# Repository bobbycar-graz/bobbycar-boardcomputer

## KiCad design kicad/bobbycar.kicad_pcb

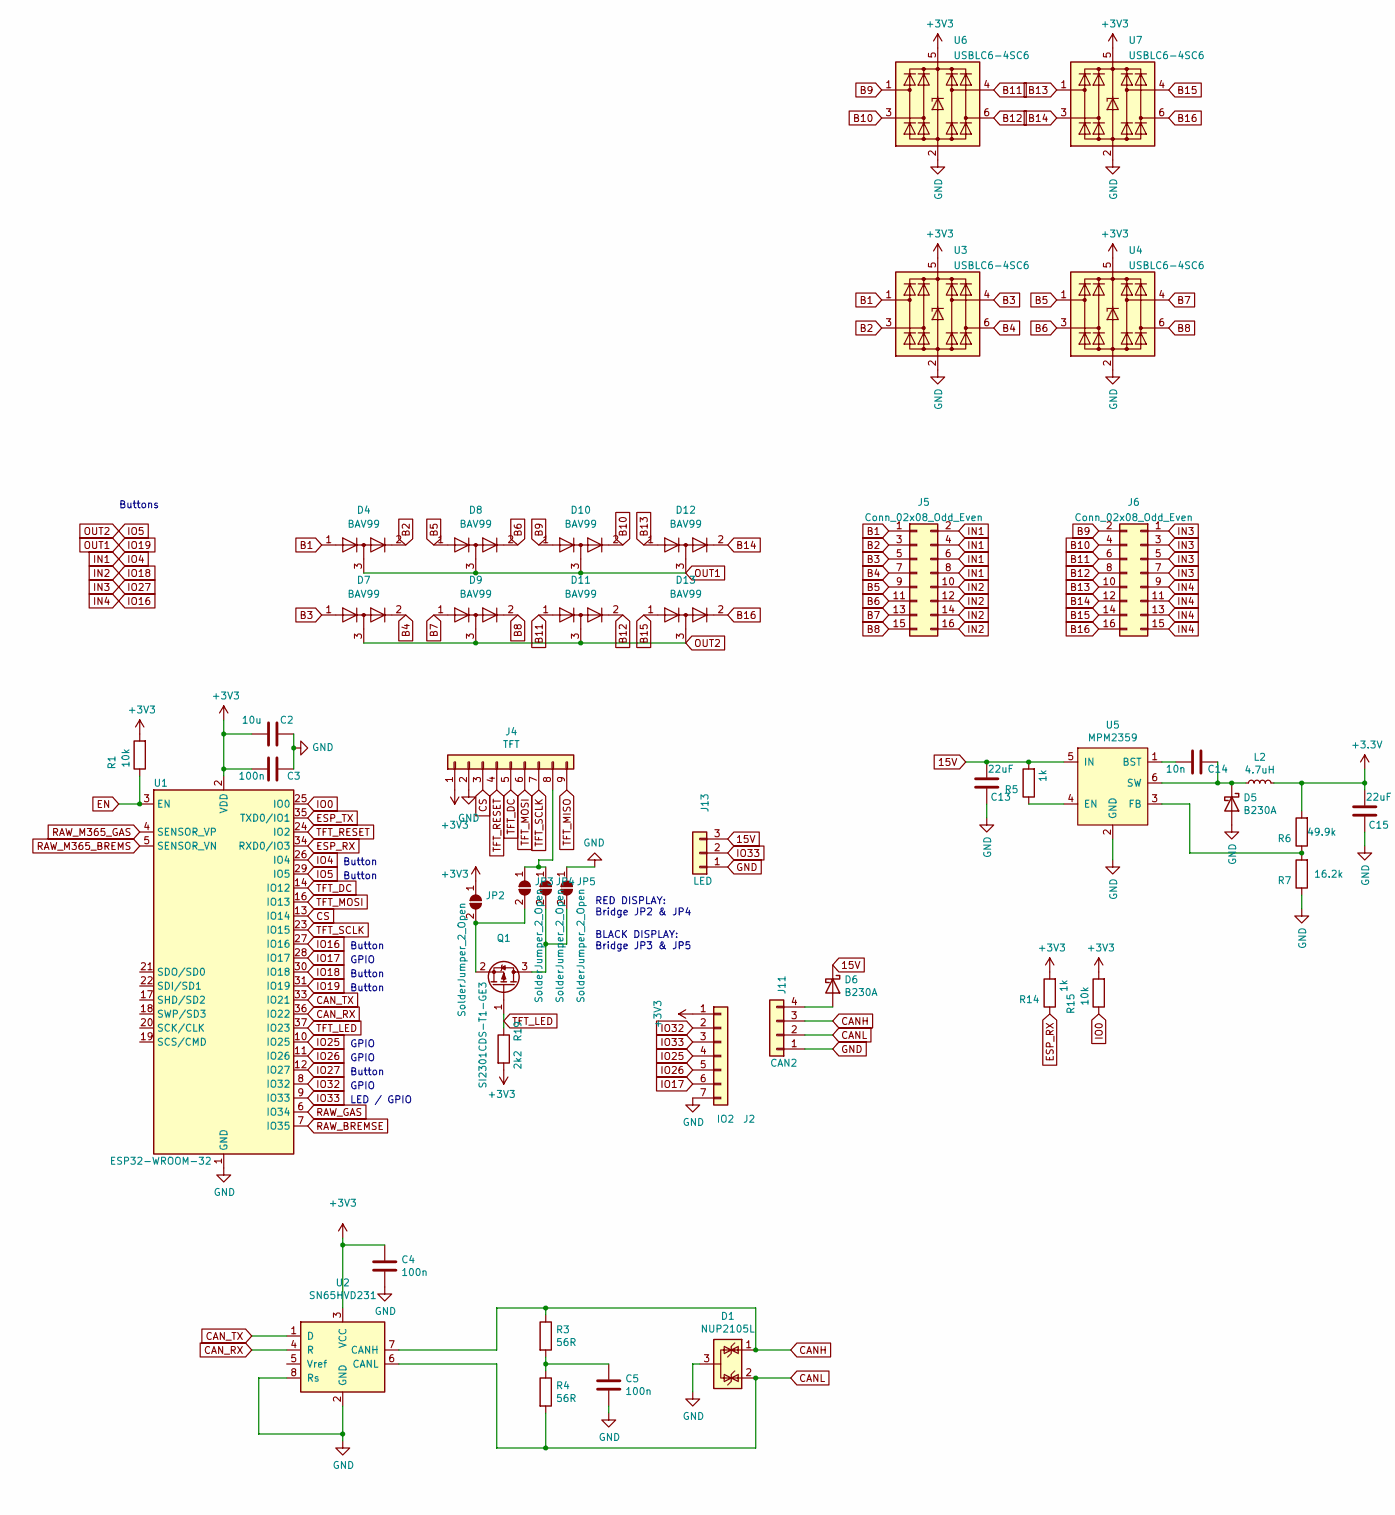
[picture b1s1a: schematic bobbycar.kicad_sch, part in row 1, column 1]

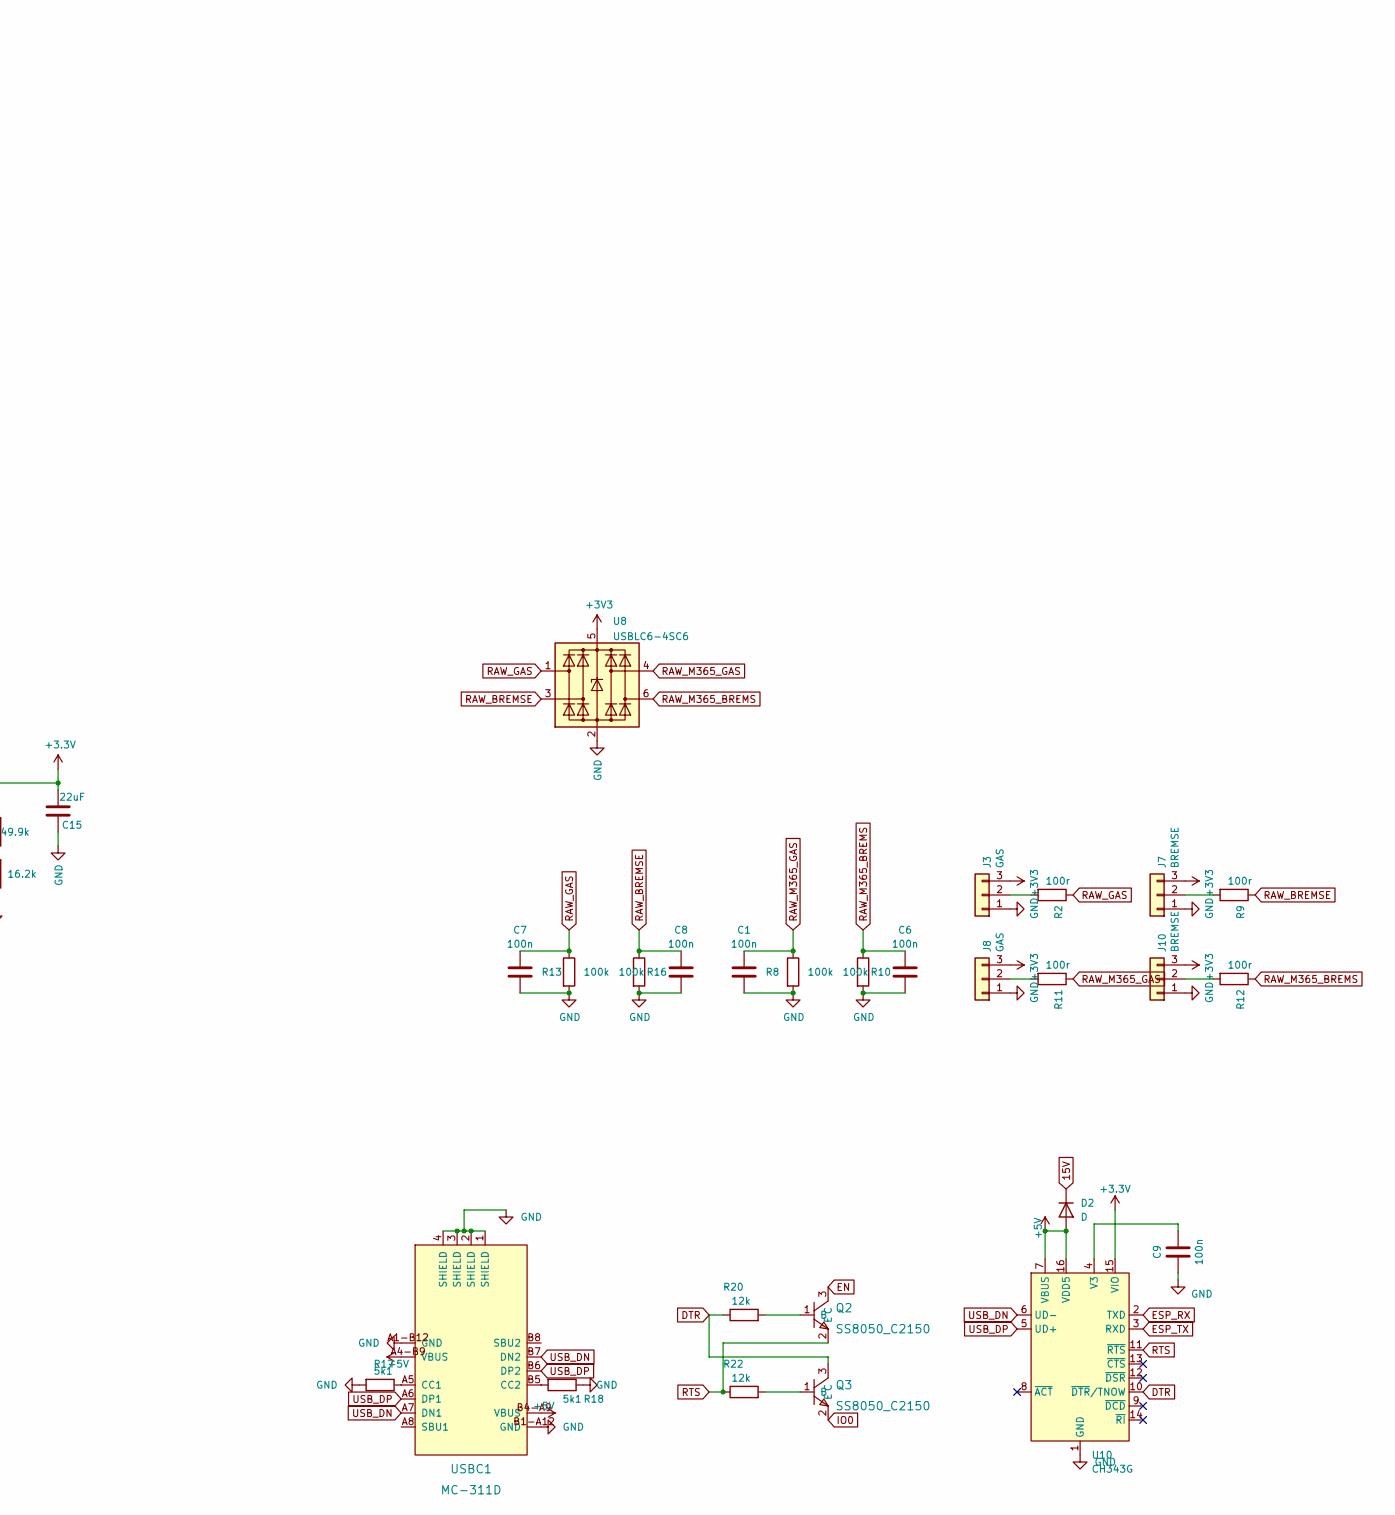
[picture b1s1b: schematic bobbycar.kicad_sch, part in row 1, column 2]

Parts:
C1, C3, C4, C5, C6, C7, C8, C9: 100n; C_0603_1608Metric; LCSC Part # C14663
C2: 10u; C_0603_1608Metric; LCSC Part # C19702
C13, C15: 22uF; C_0805_2012Metric; LCSC Part # C45783
C14: 10n; C_0603_1608Metric; LCSC Part # C57112
D1: NUP2105L; SOT-23; LCSC Part # C284104
D2: D; D_SOD-123; LCSC Part # C8598
D4: BAV99; SOT-23; LCSC Part # C2500
D5, D6: B230A; D_SMA; LCSC Part # C12889
D7, D8, D9, D10, D11, D12, D13: BAV99; SOT-23
J2: IO2; PinHeader_2x04_P2.54mm_Vertical_7Pin
J3, J8: GAS; PinHeader_1x03_P2.54mm_Vertical; LCSC Part # DNP
J4: TFT; PinSocket_1x09_P2.54mm_Vertical; LCSC Part # DNP
J5, J6: Conn_02x08_Odd_Even; PinHeader_2x08_P2.54mm_Vertical; LCSC Part # DNP
J7, J10: BREMSE; PinHeader_1x03_P2.54mm_Vertical; LCSC Part # DNP
J11: CAN2; JST_XH_B4B-XH-A_1x04_P2.50mm_Vertical; LCSC Part # C144395
J13: LED; JST_XH_B3B-XH-A_1x03_P2.50mm_Vertical
JP2, JP3, JP4, JP5: SolderJumper_2_Open; SolderJumper-2_P1.3mm_Open_RoundedPad1.0x1.5mm
L2: 4.7uH; L_5040; LCSC Part # C354606
Q1: SI2301CDS-T1-GE3; SOT-23; LCSC Part # C10487
Q2, Q3: SS8050_C2150; TSOT-23; LCSC Part C2150
R1, R15: 10k; R_0603_1608Metric; LCSC C25804
R2, R9, R11, R12: 100r; R_0603_1608Metric; LCSC Part # C22775
R3, R4: 56R; R_0603_1608Metric; LCSC Part # C25196
R5, R14: 1k; R_0603_1608Metric; LCSC Part # C21190
R6: 49.9k; R_0603_1608Metric; LCSC Part # C23184
R7: 16.2k; R_0603_1608Metric; LCSC Part # C22885
R8, R10, R13, R16: 100k; R_0603_1608Metric; LCSC Part # C21190
R17, R18: 5k1; R_0603_1608Metric; LCSC C23186
R19: 2k2; R_0603_1608Metric; LCSC Part # C4190
R20, R22: 12k; R_0603_1608Metric; LCSC C22790
U1: ESP32-WROOM-32; LCSC Part # C701343
U2: SN65HVD231; SOIC-8_3.9x4.9mm_P1.27mm; LCSC Part # C30530
U3, U4, U6, U7: USBLC6-4SC6; SOT-23-6; LCSC Part # C558419
U5: MPM2359; SOT-23-6; LCSC Part # C2959845
U8: USBLC6-4SC6; SOT-23-6
U10: CH343G; SOIC-16_3.9x9.9mm_P1.27mm; LCSC C2844153
USBC1: MC-311D; USB-C-SMD_MC-311D; LCSC Part C136423

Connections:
15V: C13.2, D2.1 (K), D6.1 (K), J13.3, R5.2, U5.5 (IN)
+5V: D2.2 (A), U10.7 (VBUS), U10.16 (VDD5), USBC1.A4-B9 (VBUS), USBC1.B4-A9 (VBUS)
B1: D4.1 (K), J5.1, U3.1 (I/O1)
B2: D4.2 (A), J5.3, U3.3 (I/O2)
B3: D7.1 (K), J5.5, U3.4 (I/O3)
B4: D7.2 (A), J5.7, U3.6 (I/O4)
B5: D8.1 (K), J5.9, U4.1 (I/O1)
B6: D8.2 (A), J5.11, U4.3 (I/O2)
B7: D9.1 (K), J5.13, U4.4 (I/O3)
B8: D9.2 (A), J5.15, U4.6 (I/O4)
B9: D10.1 (K), J6.2, U6.1 (I/O1)
B10: D10.2 (A), J6.4, U6.3 (I/O2)
B11: D11.1 (K), J6.6, U6.4 (I/O3)
B12: D11.2 (A), J6.8, U6.6 (I/O4)
B13: D12.1 (K), J6.10, U7.1 (I/O1)
B14: D12.2 (A), J6.12, U7.3 (I/O2)
B15: D13.1 (K), J6.14, U7.4 (I/O3)
B16: D13.2 (A), J6.16, U7.6 (I/O4)
CANH: D1.1 (K), J11.3, R3.1, U2.7 (CANH)
CANL: D1.2 (K), J11.2, R4.2, U2.6 (CANL)
CAN_RX: U1.36 (IO22), U2.4 (R)
CAN_TX: U1.33 (IO21), U2.1 (D)
CS: J4.3, U1.13 (IO14)
DTR: Q3.3 (C), R20.1, U10.10 (~DTR/TNOW)
EN: Q2.3 (C), R1.1, U1.3 (EN)
ESP_RX: R14.1, U1.34 (RXD0/IO3), U10.2 (TXD)
ESP_TX: U1.35 (TXD0/IO1), U10.3 (RXD)
GND: C1.1, C2.1, C3.1, C4.2, C5.2, C6.1, C7.1, C8.1, C9.1, C13.1, C15.1, D1.3 (A), D5.2 (A), J2.7, J3.1, J4.2, J7.1, J8.1, J10.1, J11.1, J13.1, JP5.1 (A), R7.1, R8.2, R10.2, R13.2, R16.2, R17.2, R18.1, U1.1 (GND), U1.15 (GND), U1.38 (GND), U1.39 (GND), U2.2 (GND), U2.8 (Rs), U3.2 (GND), U4.2 (GND), U5.2 (GND), U6.2 (GND), U7.2 (GND), U8.2 (GND), U10.1 (GND), USBC1.1 (SHIELD), USBC1.2 (SHIELD), USBC1.3 (SHIELD), USBC1.4 (SHIELD), USBC1.A1-B12 (GND), USBC1.B1-A12 (GND)
IN1: J5.2, J5.4, J5.6, J5.8, U1.26 (IO4)
IN2: J5.10, J5.12, J5.14, J5.16, U1.30 (IO18)
IN3: J6.1, J6.3, J6.5, J6.7, U1.12 (IO27)
IN4: J6.9, J6.11, J6.13, J6.15, U1.27 (IO16)
IO0: Q3.2 (E), R15.1, U1.25 (IO0)
IO5: D7.3 (K), D9.3 (K), D11.3 (K), D13.3 (K), U1.29 (IO5)
IO17: J2.6, U1.28 (IO17)
IO19: D4.3 (K), D8.3 (K), D10.3 (K), D12.3 (K), U1.31 (IO19)
IO25: J2.4, U1.10 (IO25)
IO26: J2.5, U1.11 (IO26)
IO32: J2.2, U1.8 (IO32)
IO33: J2.3, J13.2, U1.9 (IO33)
unnamed: C5.1, R3.2, R4.1
unnamed: C9.2, U10.4 (V3)
unnamed: C14.1, D5.1 (K), L2.1, U5.6 (SW)
unnamed: C14.2, U5.1 (BST)
unnamed: D6.2 (A), J11.4
unnamed: J3.2, R2.2
unnamed: J4.8, JP3.1 (A), JP4.1 (A)
unnamed: J7.2, R9.2
unnamed: J8.2, R11.2
unnamed: J10.2, R12.2
unnamed: JP2.2 (B), JP3.2 (B), Q1.2 (S)
unnamed: JP4.2 (B), JP5.2 (B), Q1.3 (D)
unnamed: Q2.1 (B), R20.2
unnamed: Q3.1 (B), R22.2
unnamed: R5.1, U5.4 (EN)
unnamed: R6.1, R7.2, U5.3 (FB)
unnamed: R17.1, USBC1.A5 (CC1)
unnamed: R18.2, USBC1.B5 (CC2)
RAW_BREMSE: C8.2, R9.1, R16.1, U1.7 (IO35), U8.3 (I/O2)
RAW_GAS: C7.2, R2.1, R13.1, U1.6 (IO34), U8.1 (I/O1)
RAW_M365_BREMS: C6.2, R10.1, R12.1, U1.5 (SENSOR_VN), U8.6 (I/O4)
RAW_M365_GAS: C1.2, R8.1, R11.1, U1.4 (SENSOR_VP), U8.4 (I/O3)
RTS: Q2.2 (E), R22.1, U10.11 (~RTS)
TFT_DC: J4.5, U1.14 (IO12)
TFT_LED: Q1.1 (G), R19.1, U1.37 (IO23)
TFT_MISO: J4.9
TFT_MOSI: J4.6, U1.16 (IO13)
TFT_RESET: J4.4, U1.24 (IO2)
TFT_SCLK: J4.7, U1.23 (IO15)
USB_DN: U10.6 (UD-), USBC1.A7 (DN1), USBC1.B7 (DN2)
USB_DP: U10.5 (UD+), USBC1.A6 (DP1), USBC1.B6 (DP2)

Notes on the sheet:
GPIO
RED DISPLAY: Bridge JP2 & JP4 BLACK DISPLAY: Bridge JP3 & JP5
Button
Buttons
LED / GPIO

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
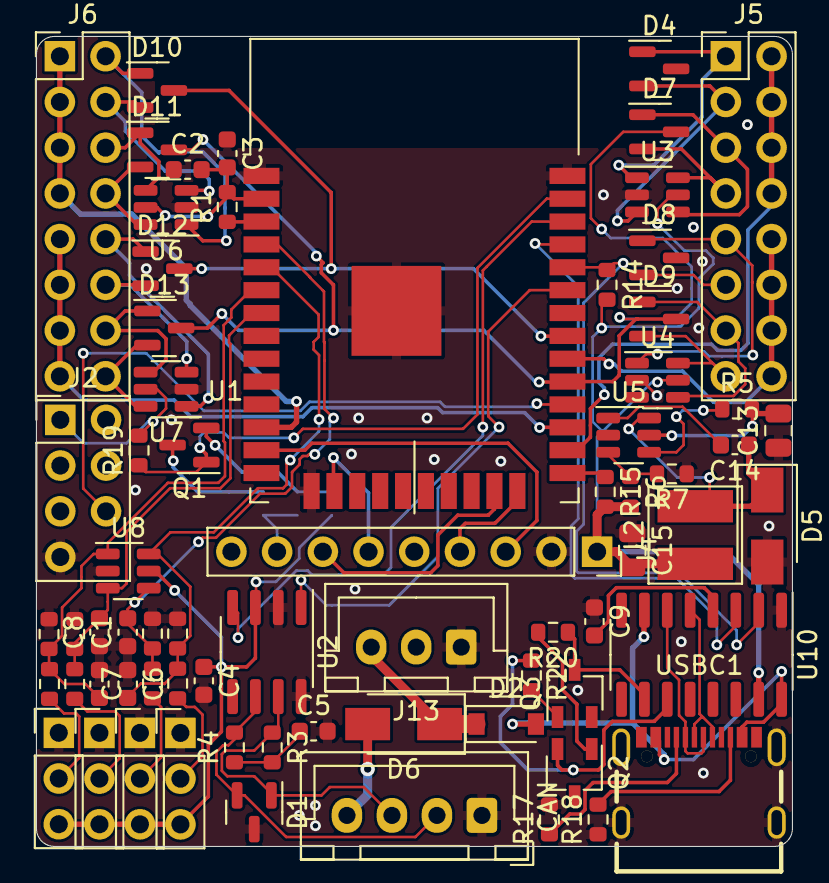
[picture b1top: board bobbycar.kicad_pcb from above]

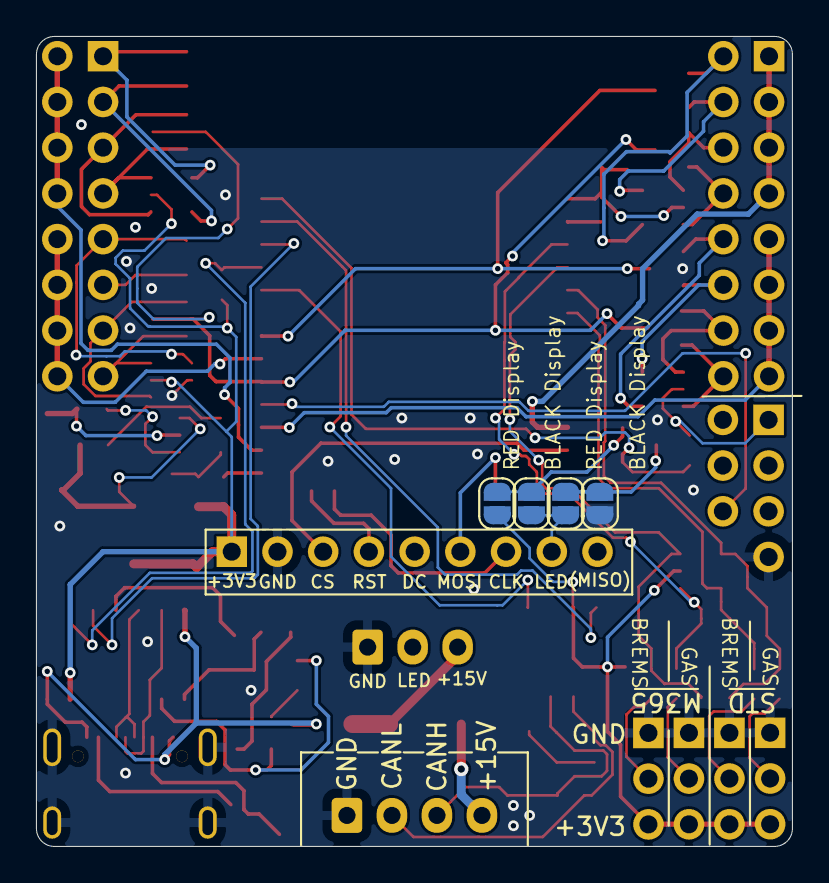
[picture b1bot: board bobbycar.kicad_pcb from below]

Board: 2 copper layers, 42.0 x 45.0 mm, 73 parts (4 on the bottom side), 71 nets.

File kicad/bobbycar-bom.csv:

Comment,Designator,Footprint,LCSC
"10n","C14","Capacitor_SMD:C_0603_1608Metric","C57112"
"22uF","C13,C15","Capacitor_SMD:C_0805_2012Metric","C45783"
"10u","C2","Capacitor_SMD:C_0603_1608Metric","C19702"
"100n","C3,C4,C5,C7,C8","Capacitor_SMD:C_0603_1608Metric","C14663"
"NUP2105L","D1","Package_TO_SOT_SMD:SOT-23","C284104"
"CDSOD323","D2,D3","Diode_SMD:D_SOD-323","C139300"
"B230A","D5,D6","Diode_SMD:D_SMA","C12889"
"IO","J1","Connector_PinHeader_2.54mm:PinHeader_1x07_P2.54mm_Vertical",""
"CAN2","J11","Connector_PinHeader_2.54mm:PinHeader_1x04_P2.54mm_Vertical",""
"PROG","J12","Connector_PinHeader_2.54mm:PinHeader_1x05_P2.54mm_Vertical",""
"IO2","J2","Connector_PinHeader_2.54mm:PinHeader_1x06_P2.54mm_Vertical",""
"GAS","J3","Connector_PinHeader_2.54mm:PinHeader_1x03_P2.54mm_Vertical",""
"TFT","J4","Connector_PinSocket_2.54mm:PinSocket_1x09_P2.54mm_Vertical",""
"BREMSE","J7","Connector_PinHeader_2.54mm:PinHeader_1x03_P2.54mm_Vertical",""
"I2C","J8","Connector_JST:JST_SH_SM04B-SRSS-TB_1x04-1MP_P1.00mm_Horizontal",""
"CAN3","J9","Connector_Molex:Molex_PicoBlade_53047-0410_1x04_P1.25mm_Vertical",""
"4.7uH","L2","boardcomputer:L_5040","C354606"
"SI2301CDS-T1-GE3","Q1","Package_TO_SOT_SMD:SOT-23","C10487"
"1k","R1,R5,R13,R14,R15,R16","Resistor_SMD:R_0603_1608Metric","C21190"
"2k2","R10,R11,R19","Resistor_SMD:R_0603_1608Metric","C4190"
"56R","R3,R4","Resistor_SMD:R_0603_1608Metric","C25196"
"49.9k","R6","Resistor_SMD:R_0603_1608Metric","C23184"
"16.2k","R7","Resistor_SMD:R_0603_1608Metric","C22885"
"100r","R2,R9","Resistor_SMD:R_0603_1608Metric","C22775"
"ESP32-WROOM-32","U1","RF_Module:ESP32-WROOM-32","C473012"
"SN65HVD231","U2","Package_SO:SOIC-8_3.9x4.9mm_P1.27mm","C30530"
"MPM2359","U5","Package_TO_SOT_SMD:SOT-23-6","C14259"

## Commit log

2020-05-24 add readme
2021-02-04 Added CAN and 5V dcdc
2021-02-16 created layout
2021-02-22 Made files production ready
2021-05-02 Added fet for led control
2021-05-31 updated picture
2021-06-01 changed dcdc added pinheaders
2021-12-14 changed to single 3.3V dcdc
2022-01-23 added new CAN connector, added diode matrix
2022-04-09 added 16 buttons
2022-04-10 Add H-bridge for beeper; convert symbol library to new format
2022-04-10 Correct part number for MOSFET driver
2022-06-12 ordered at jlcpcb
2022-10-14 Cleared pcb, added usb c
2022-10-14 Layout done
2022-10-14 Half done trace layout
2023-05-02 Remove and ignore some KiCad files
2023-05-02 Convert to KiCad 7
2023-05-02 Move buzzer stuff to sub-sheet, connect buzzer to GND instead of +15V
2023-05-02 Fix some ERC issues, use +3V3 label everywhere
2023-05-03 Move 3V3 supply to sub-sheet
2023-05-03 Use proper symbols instead of labels for GND and +15V
2023-05-03 Add capacitor to GND on EN
